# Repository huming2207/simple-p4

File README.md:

# Simple ESP32-P4 development board

## Status

~~As of 15 Sep 2025, I've just sent it out to JLCPCB for SMT, hasn't confirmed working yet.~~

Loadded via JLC SMT, confirmed working.

Do not use it for production.

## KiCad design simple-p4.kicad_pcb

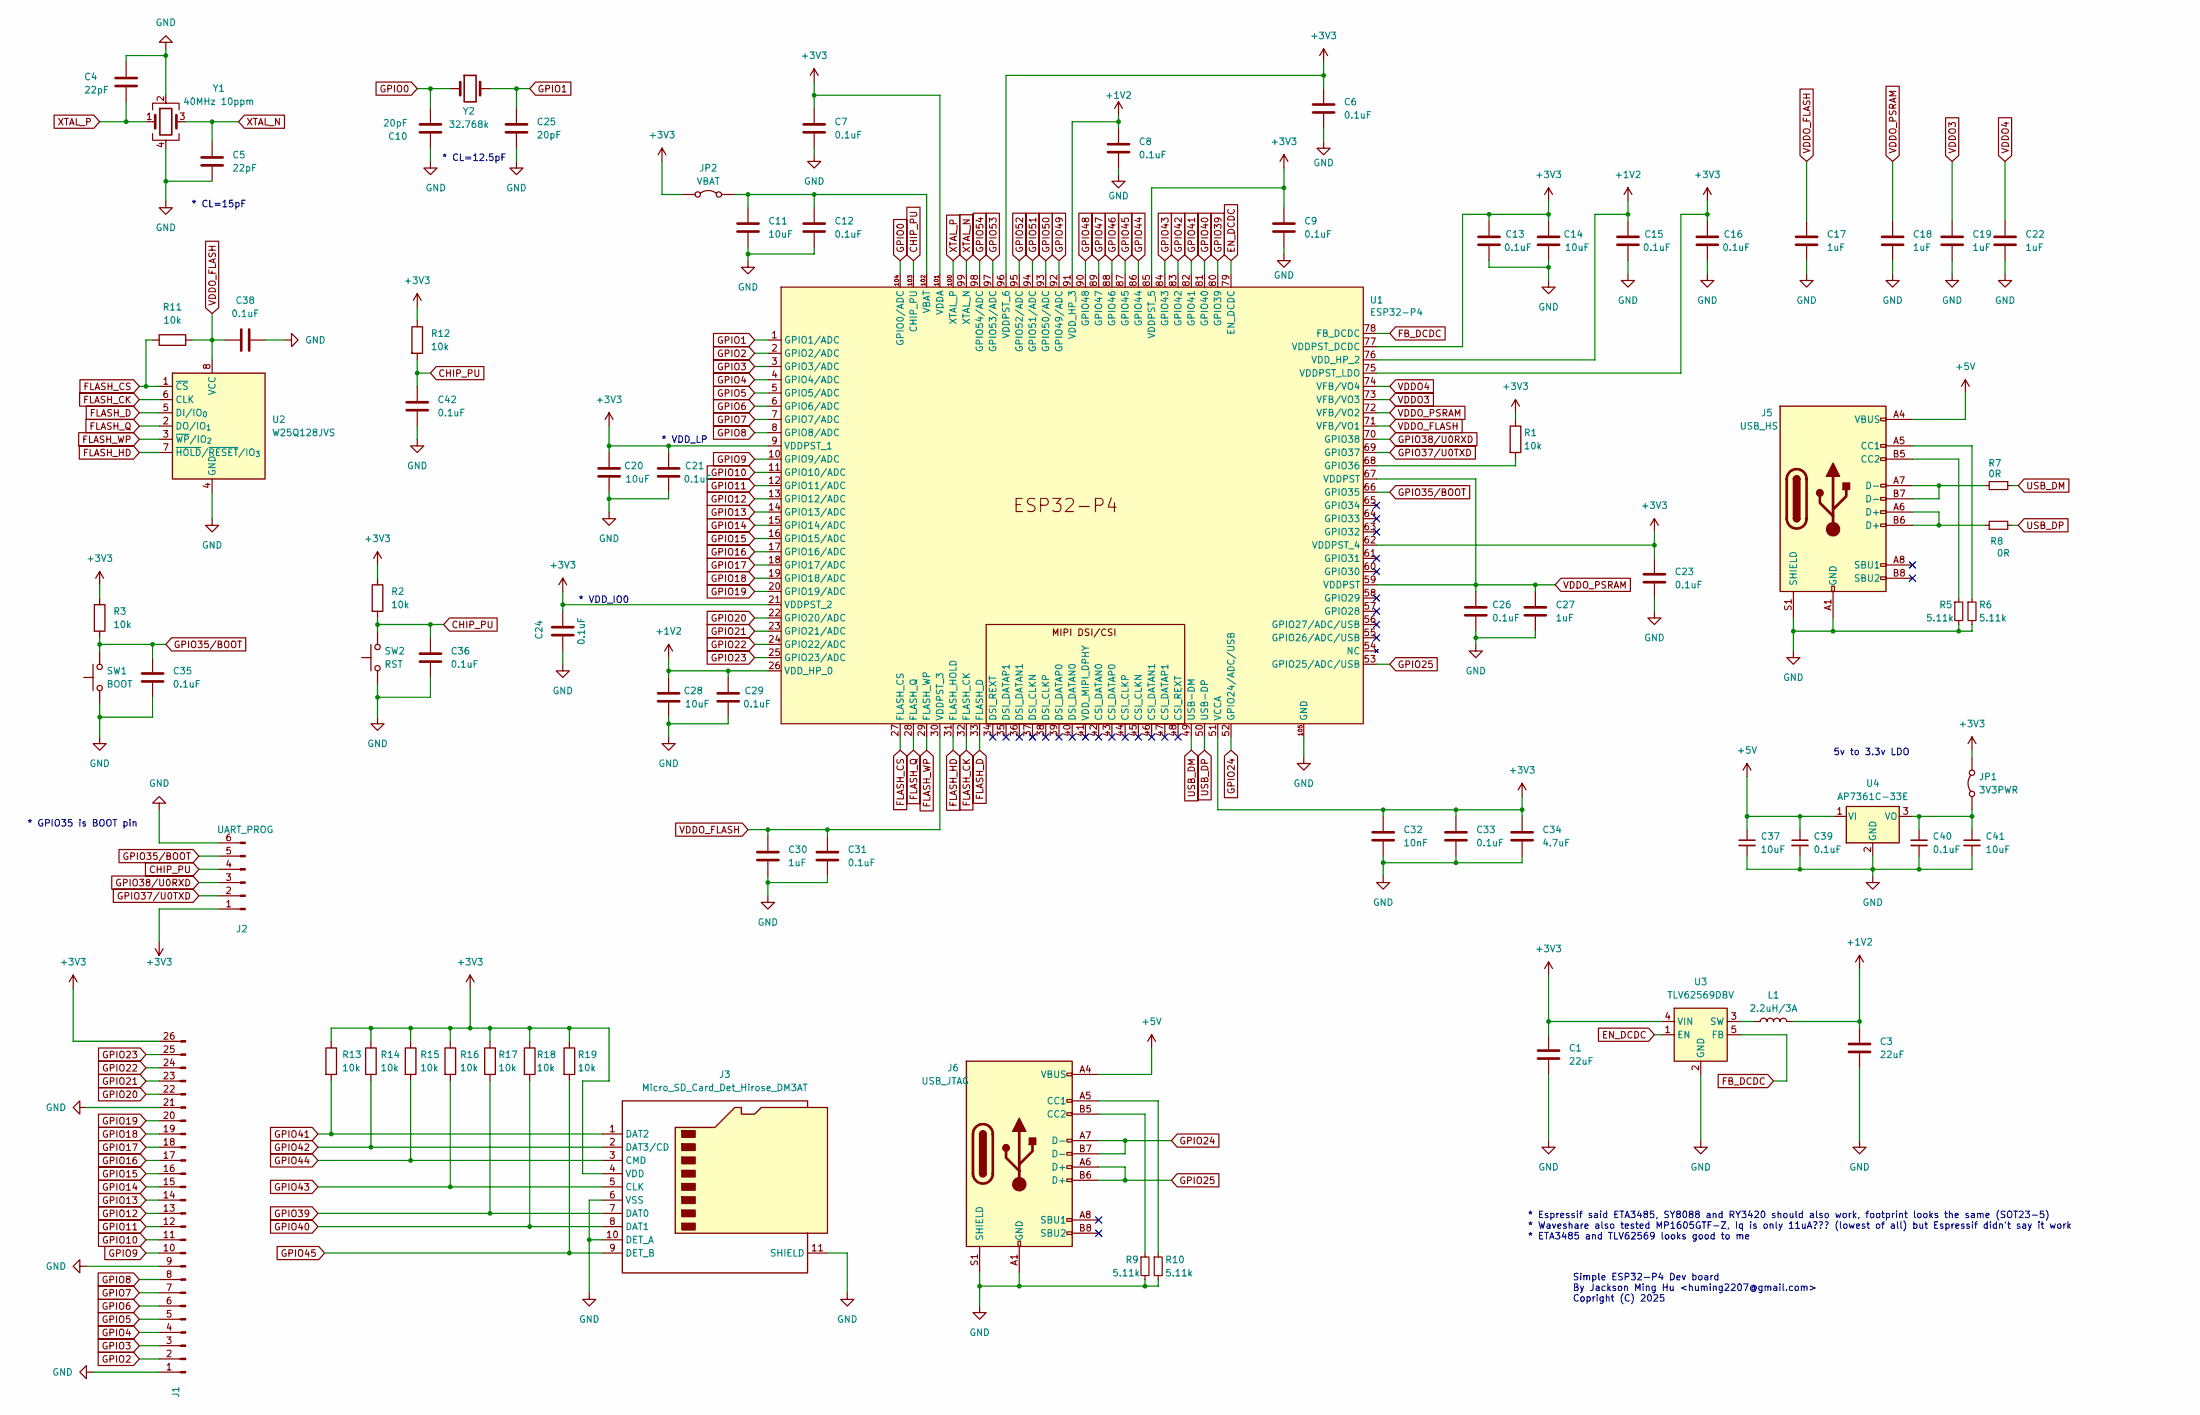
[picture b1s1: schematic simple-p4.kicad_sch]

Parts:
C1, C3: 22uF; C_0603_1608Metric
C4, C5: 22pF; C_0402_1005Metric
C6, C7, C8, C9, C12, C13, C15, C16, C21, C23, C24, C26, C29, C31, C33, C35, C36, C38, C39, C40, C42: 0.1uF; C_0402_1005Metric
C10, C25: 20pF; C_0402_1005Metric
C11, C14, C20, C28, C37, C41: 10uF; C_0603_1608Metric
C17, C18, C19, C22, C27, C30: 1uF; C_0603_1608Metric
C32: 10nF; C_0402_1005Metric
C34: 4.7uF; C_0603_1608Metric
J1: Conn_01x26_Pin; PinHeader_2x13_P2.54mm_Vertical
J2: UART_PROG; PinHeader_1x06_P2.54mm_Vertical
J3: Micro_SD_Card_Det_Hirose_DM3AT; microSD_HC_Hirose_DM3AT-SF-PEJM5
J5: USB_HS; USB_C_Receptacle_HRO_TYPE-C-31-M-12
J6: USB_JTAG; USB_C_Receptacle_HRO_TYPE-C-31-M-12
JP1: 3V3PWR; SolderJumper-2_P1.3mm_Bridged_Pad1.0x1.5mm
JP2: VBAT; SolderJumper-2_P1.3mm_Bridged_Pad1.0x1.5mm
L1: 2.2uH/3A; L_Changjiang_FTC322510S
R1, R2, R3, R11, R12, R13, R14, R15, R16, R17, R18, R19: 10k; R_0402_1005Metric
R5, R6, R9, R10: 5.11k; R_0402_1005Metric
R7, R8: 0R; R_0402_1005Metric
SW1: BOOT; SW_Push_1P1T_XKB_TS-1187A
SW2: RST; SW_Push_1P1T_XKB_TS-1187A
U1: ESP32-P4
U2: W25Q128JVS; SOIC-8_5.3x5.3mm_P1.27mm
U3: TLV62569DBV; SOT-23-5
U4: AP7361C-33E; SOT-223-3_TabPin2
Y1: 40MHz 10ppm; Crystal_SMD_2016-4Pin_2.0x1.6mm
Y2: 32.768k; Crystal_SMD_3215-2Pin_3.2x1.5mm

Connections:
+1V2: C3.1, C8.1, C15.1, C28.1, C29.1, L1.2, U1.26 (VDD_HP_0), U1.76 (VDD_HP_2), U1.91 (VDD_HP_3)
+3V3: C1.1, C6.1, C7.1, C9.1, C13.1, C14.1, C16.1, C20.1, C21.1, C23.1, C24.2, C32.1, C33.1, C34.1, J1.26, J2.1, J3.4 (VDD), JP1.2 (B), JP2.1 (A), R1.1, R2.1, R3.1, R12.1, R13.1, R14.1, R15.1, R16.1, R17.1, R18.1, R19.1, U1.9 (VDDPST_1), U1.21 (VDDPST_2), U1.51 (VCCA), U1.62 (VDDPST_4), U1.75 (VDDPST_LDO), U1.77 (VDDPST_DCDC), U1.85 (VDDPST_5), U1.96 (VDDPST_6), U1.101 (VDDA), U3.4 (VIN)
+5V: C37.1, C39.1, J5.A4 (VBUS), J5.A9 (VBUS), J5.B4 (VBUS), J5.B9 (VBUS), J6.A4 (VBUS), J6.A9 (VBUS), J6.B4 (VBUS), J6.B9 (VBUS), U4.1 (VI)
CHIP_PU: C36.1, C42.1, J2.4, R2.2, R12.2, SW2.2, U1.103 (CHIP_PU)
EN_DCDC: U1.79 (EN_DCDC), U3.1 (EN)
FB_DCDC: U1.78 (FB_DCDC), U3.5 (FB)
FLASH_CK: U1.32 (FLASH_CK), U2.6 (CLK)
FLASH_CS: R11.1, U1.27 (FLASH_CS), U2.1 (~CS)
FLASH_D: U1.33 (FLASH_D), U2.5 (DI/IO_{0})
FLASH_HD: U1.31 (FLASH_HOLD), U2.7 (~HOLD/~RESET/IO_{3})
FLASH_Q: U1.28 (FLASH_Q), U2.2 (DO/IO_{1})
FLASH_WP: U1.29 (FLASH_WP), U2.3 (~WP/IO_{2})
GND: C1.2, C3.2, C4.1, C5.2, C6.2, C7.2, C8.2, C9.2, C10.1, C11.2, C12.2, C13.2, C14.2, C15.2, C16.2, C17.2, C18.2, C19.2, C20.2, C21.2, C22.2, C23.2, C24.1, C25.2, C26.2, C27.2, C28.2, C29.2, C30.2, C31.2, C32.2, C33.2, C34.2, C35.2, C36.2, C37.2, C38.2, C39.2, C40.2, C41.2, C42.2, J1.1, J1.9, J1.21, J2.6, J3.6 (VSS), J3.10 (DET_A), J3.11 (SHIELD), J5.A1 (GND), J5.A12 (GND), J5.B1 (GND), J5.B12 (GND), J5.S1 (SHIELD), J6.A1 (GND), J6.A12 (GND), J6.B1 (GND), J6.B12 (GND), J6.S1 (SHIELD), R5.2, R6.2, R9.2, R10.2, SW1.1, SW2.1, U1.105 (GND), U2.4 (GND), U3.2 (GND), U4.2 (GND), Y1.2, Y1.4
GPIO0: C10.2, U1.104 (GPIO0/ADC), Y2.1
GPIO1: C25.1, U1.1 (GPIO1/ADC), Y2.2
GPIO2: J1.2, U1.2 (GPIO2/ADC)
GPIO3: J1.3, U1.3 (GPIO3/ADC)
GPIO4: J1.4, U1.4 (GPIO4/ADC)
GPIO5: J1.5, U1.5 (GPIO5/ADC)
GPIO6: J1.6, U1.6 (GPIO6/ADC)
GPIO7: J1.7, U1.7 (GPIO7/ADC)
GPIO8: J1.8, U1.8 (GPIO8/ADC)
GPIO9: J1.10, U1.10 (GPIO9/ADC)
GPIO10: J1.11, U1.11 (GPIO10/ADC)
GPIO11: J1.12, U1.12 (GPIO11/ADC)
GPIO12: J1.13, U1.13 (GPIO12/ADC)
GPIO13: J1.14, U1.14 (GPIO13/ADC)
GPIO14: J1.15, U1.15 (GPIO14/ADC)
GPIO15: J1.16, U1.16 (GPIO15/ADC)
GPIO16: J1.17, U1.17 (GPIO16/ADC)
GPIO17: J1.18, U1.18 (GPIO17/ADC)
GPIO18: J1.19, U1.19 (GPIO18/ADC)
GPIO19: J1.20, U1.20 (GPIO19/ADC)
GPIO20: J1.22, U1.22 (GPIO20/ADC)
GPIO21: J1.23, U1.23 (GPIO21/ADC)
GPIO22: J1.24, U1.24 (GPIO22/ADC)
GPIO23: J1.25, U1.25 (GPIO23/ADC)
GPIO24: J6.A7 (D-), J6.B7 (D-), U1.52 (GPIO24/ADC/USB)
GPIO25: J6.A6 (D+), J6.B6 (D+), U1.53 (GPIO25/ADC/USB)
GPIO35/BOOT: C35.1, J2.5, R3.2, SW1.2, U1.66 (GPIO35)
GPIO37/U0TXD: J2.2, U1.69 (GPIO37)
GPIO38/U0RXD: J2.3, U1.70 (GPIO38)
GPIO39: J3.7 (DAT0), R17.2, U1.80 (GPIO39)
GPIO40: J3.8 (DAT1), R18.2, U1.81 (GPIO40)
GPIO41: J3.1 (DAT2), R13.2, U1.82 (GPIO41)
GPIO42: J3.2 (DAT3/CD), R14.2, U1.83 (GPIO42)
GPIO43: J3.5 (CLK), R16.2, U1.84 (GPIO43)
GPIO44: J3.3 (CMD), R15.2, U1.86 (GPIO44)
GPIO45: J3.9 (DET_B), R19.2, U1.87 (GPIO45)
GPIO46: U1.88 (GPIO46)
GPIO47: U1.89 (GPIO47)
GPIO48: U1.90 (GPIO48)
GPIO49: U1.92 (GPIO49/ADC)
GPIO50: U1.93 (GPIO50/ADC)
GPIO51: U1.94 (GPIO51/ADC)
GPIO52: U1.95 (GPIO52/ADC)
GPIO53: U1.97 (GPIO53/ADC)
GPIO54: U1.98 (GPIO54/ADC)
unnamed: J5.A5 (CC1), R6.1
unnamed: J5.B5 (CC2), R5.1
unnamed: J5.A6 (D+), J5.B6 (D+), R8.1
unnamed: J5.A7 (D-), J5.B7 (D-), R7.2
unnamed: J6.A5 (CC1), R10.1
unnamed: J6.B5 (CC2), R9.1
unnamed: C40.1, C41.1, JP1.1 (A), U4.3 (VO)
unnamed: C11.1, C12.1, JP2.2 (B), U1.102 (VBAT)
unnamed: R1.2, U1.68 (GPIO36)
unnamed: L1.1, U3.3 (SW)
USB_DM: R7.1, U1.49 (USB-DM)
USB_DP: R8.2, U1.50 (USB-DP)
VDDO3: C19.1, U1.73 (VFB/VO3)
VDDO4: C22.1, U1.74 (VFB/VO4)
VDDO_FLASH: C17.1, C30.1, C31.1, C38.1, R11.2, U1.30 (VDDPST_3), U1.71 (VFB/VO1), U2.8 (VCC)
VDDO_PSRAM: C18.1, C26.1, C27.1, U1.59 (VDDPST), U1.67 (VDDPST), U1.72 (VFB/VO2)
XTAL_N: C5.1, U1.99 (XTAL_N), Y1.3
XTAL_P: C4.2, U1.100 (XTAL_P), Y1.1

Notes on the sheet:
* VDD_IO0
* CL=12.5pF
Simple ESP32-P4 Dev board By Jackson Ming Hu <huming2207@gmail.com> Copright (C) 2025
5v to 3.3v LDO
* VDD_LP
* CL=15pF
* GPIO35 is BOOT pin
* Espressif said ETA3485, SY8088 and RY3420 should also work, footprint looks the same (SOT23-5) * Waveshare also tested MP1605GTF-Z, Iq is only 11uA??? (lowest of all) but Espressif didn't say it work * ETA3485 and TLV62569 looks good to me

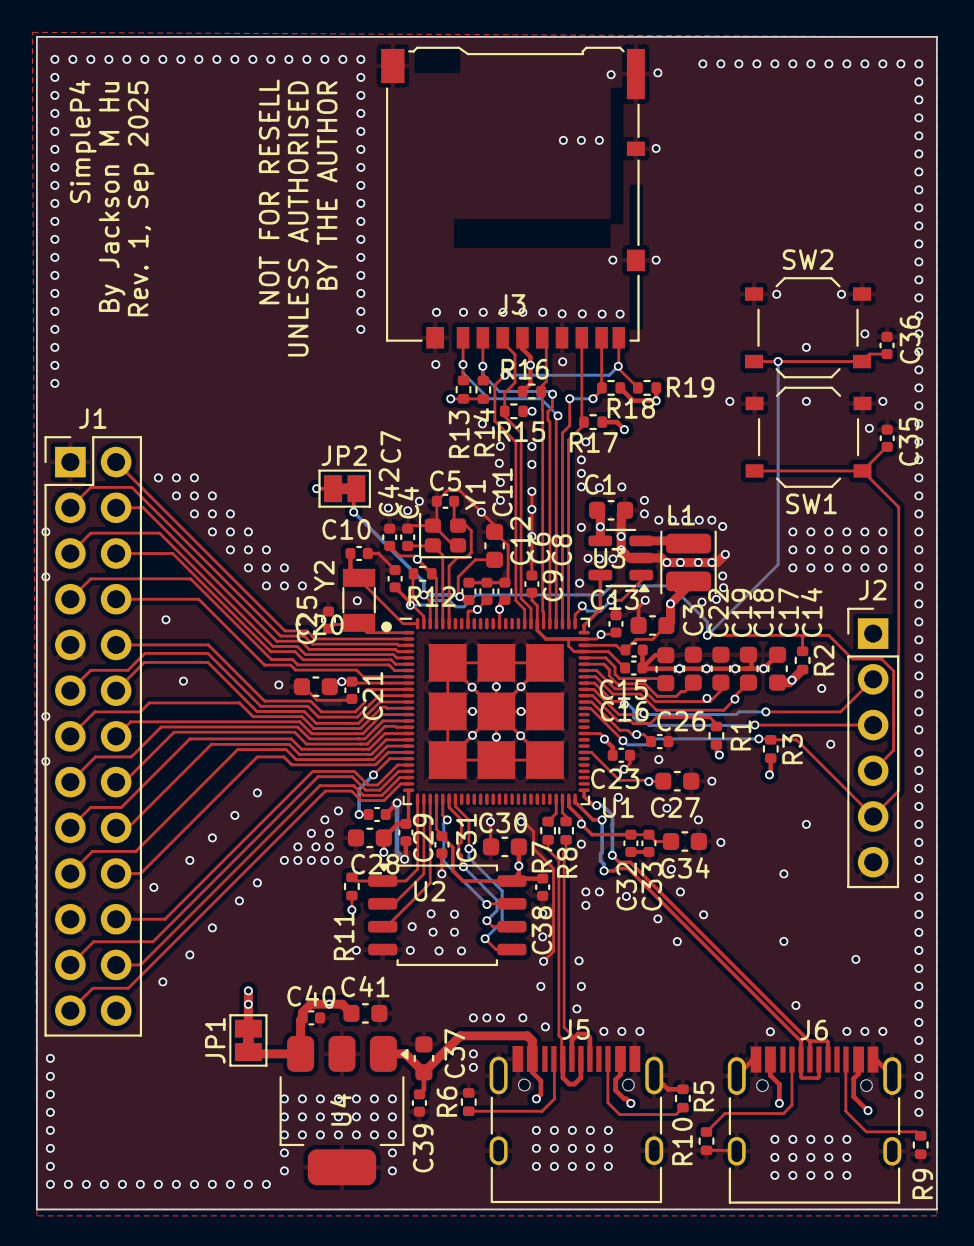
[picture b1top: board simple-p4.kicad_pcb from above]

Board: 4 copper layers, 50.0 x 65.1 mm, 75 parts (0 on the bottom side), 67 nets.

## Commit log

2025-09-03 Init
2025-09-04 Implement schematic for basic ESP32-P4 nets
2025-09-06 schematic: add crystal
2025-09-07 schematic: add USB port
2025-09-10 Finish PCB
2025-09-11 Finish off PCB
2025-09-14 Finish off rev. 1
2025-09-22 Update rev1 PDF schematic
